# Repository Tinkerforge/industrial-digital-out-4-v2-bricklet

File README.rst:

Industrial Digital Out 4 Bricklet 2.0
=====================================

This repository contains the firmware source code and the hardware design
files. The documentation generator configs can be found at
https://github.com/Tinkerforge/generators

Repository Content
------------------

software/:
 * examples/: Examples for all supported languages
 * build/: Compiled files
 * src/: Source code of firmware
 * Makefile: Makefile to build project

hardware/:
 * Contains KiCad project files and additionally schematics as PDF

datasheets/:
 * Contains datasheets for sensors and complex ICs that are used

Hardware
--------

The hardware is designed with the open source EDA Suite KiCad
(http://www.kicad.org). Before you are able to open the files,
you have to install the Tinkerforge kicad-libraries
(https://github.com/Tinkerforge/kicad-libraries). You can either clone
them directly in hardware/ or clone them in a separate folder and
symlink them into hardware/
(ln -s kicad_path/kicad-libraries project_path/hardware). After that you
can open the .pro file in hardware/ with KiCad and from there view and
modify the schematics and the PCB layout.

Software
--------

If you want to do your own Brick/Bricklet firmware development we highly
recommend that you use our build environment setup script and read the
tutorial (https://www.tinkerforge.com/en/doc/Tutorials/Tutorial_Build_Environment/Tutorial.html).

To compile the C code we recommend you to install the newest GNU Arm Embedded
Toolchain (https://launchpad.net/gcc-arm-embedded/+download).
You also need to install bricklib2 (https://github.com/Tinkerforge/bricklib2).

You can either clone it directly in software/src/ or clone it in a
separate folder and symlink it into software/src/
(ln -s bricklib_path/bricklib2 project_path/software/src/). Finally make sure to
have CMake installed (http://www.cmake.org/cmake/resources/software.html).

After that you can build the firmware by invoking make in software/.
The firmware (.zbin) can then be found in software/build/ and uploaded
with brickv (click button "Flashing" on start screen).

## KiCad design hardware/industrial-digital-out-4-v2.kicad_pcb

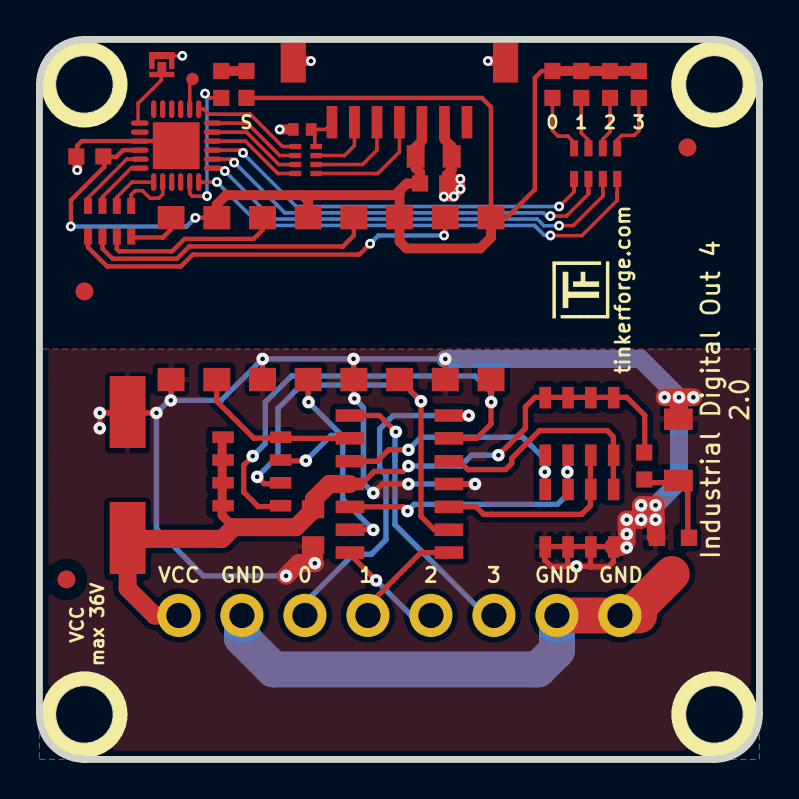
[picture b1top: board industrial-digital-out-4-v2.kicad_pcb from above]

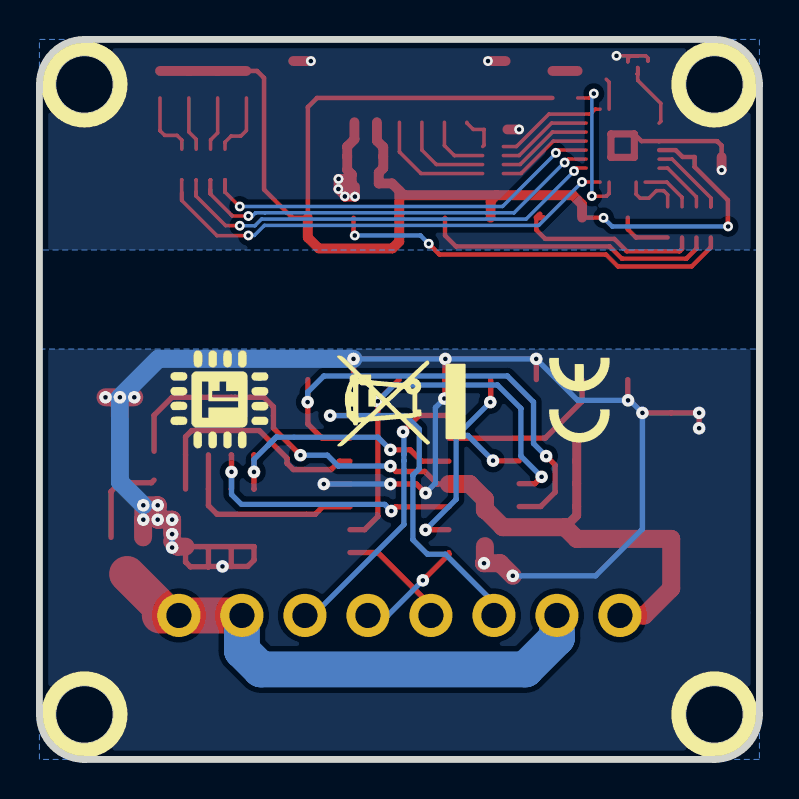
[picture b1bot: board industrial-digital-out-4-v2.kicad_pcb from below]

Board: 2 copper layers, 40.0 x 40.0 mm, 37 parts (2 on the bottom side), 46 nets.

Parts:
C1: 10uF; C0805
C2: 100nF; C0805
C3: 68µF/50V; ELKO_83
C4: 220pF; C0402F
C5: 1uF; C0603F
C6: 100nF; C0603F
D1: Z12V; MiniMelf
D2, D3, D4, D5, D6: blue; D0603F
Fiducial_Mark: VAL**; Fiducial_Mark
Fiducial_Mark#2, Fiducial_Mark#3: VAL**; Fiducial_Mark
P1: CON-SENSOR2
P2: Digital Output; OQ_8P
P3: DEBUG; DEBUG_PAD
P4: BOOT; SolderJumper
Q1: FDN5630; SOT23GDS
R1: 100k; R0603F
R2: 1k; R0603F
RP1, RP6: 1k; 0603X4
RP2: 12k; 1206X4
RP3, RP4: 10k; 1206X4
RP5: 82; 4X0402
U1: XMC1100; QFN24-4x4mm-0.5mm
U2: LTV846S; OPTO-SMD16
U3: OPA4171AIDR; SOP14
U4, U5, U6, U7: DRILL; DRILL_NP
VAL: WEEE_7mm
VAL#2: CE_5mm

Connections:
3V3: C1.1, C5.1, C6.1, D2.1, D3.1, D4.1, D5.1, D6.1, P1.3, U1.10, U2.1, U2.3, U2.5, U2.7
AGND: C2.2, C3.2, D1.1, Q1.S, RP4.1, RP4.2, RP4.3, RP4.4, U2.9, U2.11, U2.13, U2.15, U3.11
GND: C1.2, C4.2, C5.2, C6.2, P1.2, P1.EP, P4.1, U1.9, U1.EXP
unnamed: C4.1, P1.7, RP5.4
unnamed: D1.2, Q1.G, R1.2
unnamed: D2.2, R2.2
unnamed: D3.2, RP6.8
unnamed: D4.2, RP6.7
unnamed: D5.2, RP6.6
unnamed: D6.2, RP6.5
unnamed: P1.4, RP5.1
unnamed: P1.5, RP5.2
unnamed: P1.6, RP5.3
unnamed: P2.2, P2.7, P2.8, Q1.D
unnamed: P2.3, U3.14
unnamed: P2.4, U3.8
unnamed: P2.5, U3.7
unnamed: P2.6, U3.1
unnamed: P3.1, U1.2
unnamed: P4.2, U1.7
unnamed: R2.1, U1.17
unnamed: RP1.1, U2.2
unnamed: RP1.2, U2.4
unnamed: RP1.3, U2.6
unnamed: RP1.4, U2.8
unnamed: RP2.1, U2.16, U3.13
unnamed: RP2.2, U2.14, U3.9
unnamed: RP2.3, U2.12, U3.6
unnamed: RP2.4, U2.10, U3.2
unnamed: RP3.1, RP4.8, U3.3
unnamed: RP3.2, RP4.7, U3.5
unnamed: RP3.3, RP4.6, U3.10
unnamed: RP3.4, RP4.5, U3.12
unnamed: RP6.1, U1.21
unnamed: RP6.2, U1.20
unnamed: RP6.3, U1.19
unnamed: RP6.4, U1.18
OUTPUT1: RP1.5, U1.14
OUTPUT2: RP1.6, U1.13
OUTPUT3: RP1.7, U1.12
OUTPUT4: RP1.8, U1.11
S-CLK: RP5.7, U1.23
S-CS: RP5.8, U1.22
S-MISO: RP5.5, U1.1
S-MOSI: RP5.6, U1.24
VPP: C2.1, C3.1, P2.1, R1.1, RP2.5, RP2.6, RP2.7, RP2.8, RP3.5, RP3.6, RP3.7, RP3.8, U3.4

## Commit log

2018-01-17 Add datasheet
2018-01-17 Add schematic
2018-01-17 Add pcb
2018-02-20 Add .gitignore
2018-02-20 Cleanup KiCad libraries config
    Ensure LibDir=kicad-libraries and LibName1=tinkerforge.
    Remove special library.
2018-05-07 Rename files
2018-05-07 Adapt routing for status leds
2018-05-07 Change routing
2018-05-16 drc check for prototype order
2018-05-28 Firmware implementation
2018-05-29 Remove unnecessary get-selected-value function
2018-06-05 Add implementation of PWM API
2018-06-06 set origin
2018-06-18 Change capacitor footprint(s) to C0402F
2018-06-28 Fix readme
2018-07-11 Add Makefile with docker support
2018-07-11 Remove obsolete generate_makefile scripts
2018-07-11 Update directory structure and build instructions
2018-07-17 specify processor
2018-07-31 Add 3d model (*.FCStd & *.step)
2018-09-10 Add examples
2018-09-21 Use common name for channel index parameter
2018-10-02 Add BOOTLOADER_FIX_POINTER_END define
2018-10-04 Add rev to changelog
2018-10-04 Fix major version
2018-10-04 Fix 2.0.0 rev
2018-10-16 Remove in-development marker
2018-11-06 Add rust examples
2018-11-07 rust: Accept host names for ip connection, fix naming inconsistencies
2018-12-14 Add go examples.
2018-12-18 go: Change import path.
2018-12-18 go: Change import path again.
2018-12-20 rust: Reformat examples.
2019-01-24 mqtt: Add examples.
2019-01-24 mqtt: Fix example header.
2019-01-24 mqtt: Remove executable bit in example permissions.
2019-01-24 go: Minor example fixes.
2019-01-24 mqtt: Minor example fixes.
2019-01-29 rust: Fix unused loop index.
2019-03-28 c: Examples: Pre-declare array used as parameter.
2019-05-07 Abort active monoflop on set-(selected-)value call
    Don't clear monoflop time on monoflop done/abort to match documentation.
2019-05-29 Increase version for new release (changes in bricklib2)
2020-01-13 examples: Use python3 input instead of python2 raw_input.
2020-01-13 examples: mqtt: Remove trailing whitespace.
2020-02-26 drc and fixed board outline
2020-03-16 Whitespace
2020-03-23 mqtt: Update for loop style
2020-04-07 examples: rust: Always block when calling bindings functions.
2020-08-19 Add uc examples.
2020-08-25 uc: Fix whitespace
2020-08-27 uc: Fix warnings.
2020-09-02 uc: Add example driver note.
2020-10-20 Simplify the code (no functional changes)
    This is to save some flash and to allow easier Wiegand integration
2020-10-20 Add Wiegand writer support
2020-10-20 Increment firmware version for Wiegand support release
2020-10-22 wiegand: Add C test
2021-01-12 wiegand: Add Java test
2021-10-25 Update KiCad link
    https://www.kicad.org/blog/2021/10/Avoid-links-to-former-kicad-domain/
2022-04-19 examples: uc: Rename TF_HalContext to TF_HAL.
2022-04-27 uc: Adapt to bindings changes
2022-07-06 Add license files.
2023-01-30 Data Cleanup
2025-10-04 Fix compatibility with new Docker build image (GCC 14.2.1)

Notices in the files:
hardware/industrial-digital-out-4-v2.kicad_pcb:
Licensed under CERN OHL v.1.1
Copyright (©) 2023, T.Schneidermann
Copyright Tinkerforge GmbH 2023.
This documentation describes Open Hardware and is licensed under the
CERN OHL v. 1.1.
